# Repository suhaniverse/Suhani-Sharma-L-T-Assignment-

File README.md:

# Suhani-Sharma-L-T-Assignment-

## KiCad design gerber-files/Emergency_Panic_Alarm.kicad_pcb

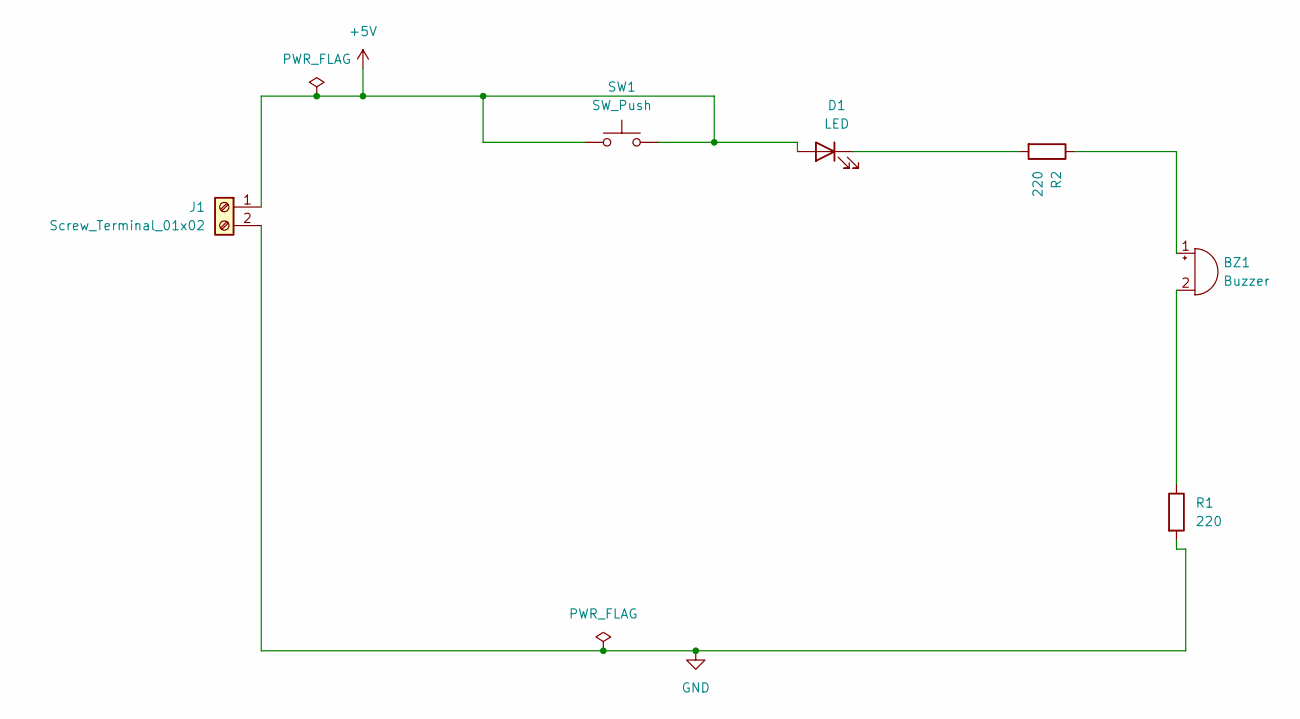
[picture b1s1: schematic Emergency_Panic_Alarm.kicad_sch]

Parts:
BZ1: Buzzer; Buzzer_12x9.5RM7.6
D1: LED; LED_D5.0mm
J1: Screw_Terminal_01x02; TerminalBlock_MaiXu_MX126-5.0-02P_1x02_P5.00mm
R1, R2: 220; R_Axial_DIN0204_L3.6mm_D1.6mm_P7.62mm_Horizontal
SW1: SW_Push; SW_PUSH_6mm

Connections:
+5V: D1.2 (A), J1.1, SW1.1, SW1.2
GND: J1.2, R1.2
unnamed: BZ1.1 (+), R2.1
unnamed: BZ1.2 (-), R1.1
unnamed: D1.1 (K), R2.2

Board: 2 copper layers, 6 parts (0 on the bottom side), 5 nets, no tracks yet.
